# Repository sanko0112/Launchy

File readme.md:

### ESP32 ESP-NOW Based model rocket launch controller

## 🤌Features

- ESP-NOW Long range protocol
- Multi-layer safety: Key switch, iButton, push button
- OLED display for status feedback
- Built in battery charging circuit (TP4056)
- USB-C for programming/charging
- Internal 1S / External 2S battery selection for the e-match
- Continuity test (1S mode)
- Preheat mode(1S mode)
- Configurabe Countdown time, Ignition time
## 🔧Hardware

&nbsp;&nbsp;&nbsp;&nbsp;&nbsp;The system is based on a custom PCB designed in KiCad, built around the ESP32-C3-MINI-1 module. Both the transmitter and the igniter/receiver use the same board design, but are populated with different component sets depending on their role. The
hardware integrates Li-Ion charging (TP4056), a 3.3 V LDO regulator (AP2112K), a MOSFET-driven relay interface, iButton authentication, and status LEDs. USB-C is provided for charging and programming, while screw terminals allow safe connection of the igniter circuit.

&nbsp;&nbsp;&nbsp;&nbsp;&nbsp;Complete manufacturing files are available as a ZIP inside the GERBER folder as well as the BoM. Symbol and footprint libraries are uploaded so the project should be fully editable in KiCad now.

## 💻Firmware
### Transmitter.ino
- Handles the remote unit (user interface + iButton authentication).
- Implements menus for:
    - Battery type selection
    - Continuity check
    - Countdown time
    - Preheat start time
    - Preheat duration
    - Ignition delta
- Uses ESP-NOW to send launch and continuity test commands
- Provides OLED display feedback via LaunchDisplayLibrary
- Requires valid iButton for arming and launch
### Receiver.ino
- Handles the receiver unit (relay + buzzer)
- Waits for commands over ESP-NOW
- Performs continuity test by measuring V<sub>drop<sub>
- Executes countdown, preheat, and ignition relay control
- Includes buzzer startup sounds and launch feedback
### LaunchDisplayLibrary
- Custom display driver using U8g2 for SH1106 OLED.
- Provides functions for:
    - Splash/welcome screen
    - Authentication animations
    - Armed state screen (with T-, P_s, P_d, I_d values)
    - Countdown + preheat visual feedback
    - Ignition screen
    - Menus for parameter selection
### GetMacAddress.ino
- Utility to print the ESP32’s MAC address (used for setting ESP-NOW peers).
### ReadFob.ino
- Utility to read and print iButton IDs (used to whitelist authorized keys).
### Dependencies
#### [Arduino Core for ESP32](https://github.com/espressif/arduino-esp32)
### Libraries:
- esp_now.h (built-in)
- WiFi.h (built-in)
- esp_wifi.h (for long-range protocol mode)
- OneWire (for iButton reader)
- U8g2lib (for OLED display)
## 🚀 Setup & Upload
1. Clone repo and open in Arduino IDE.
2. Select ESP32 Dev Module (or your ESP32 board).
3. Upload separately:
    - Transmitter.ino → Remote unit
    - 2.Receiver.ino → Receiver unit
4. Use GetMacAddress.ino on each ESP32 to note their MAC addresses.
    - Update broadcastAddress[] in transmitter/receiver code accordingly.
5. Use Read_fob.ino to read your iButton ID.
    - Replace in allowedID[] array in the transmitter code.
## 📺 Display demo

## 🔒 Safety

- Relay will not activate without valid iButton authentication.
- Launch packets use a session_id to prevent accidental re-triggering.
- Continuity test ensures igniter is properly connected before launch, if fails the system enters failsafe, requires full restart
## ✏️Schematic

## 📷Images

### Transmitter

### Igniter

### Accessories

## 🎥Demo

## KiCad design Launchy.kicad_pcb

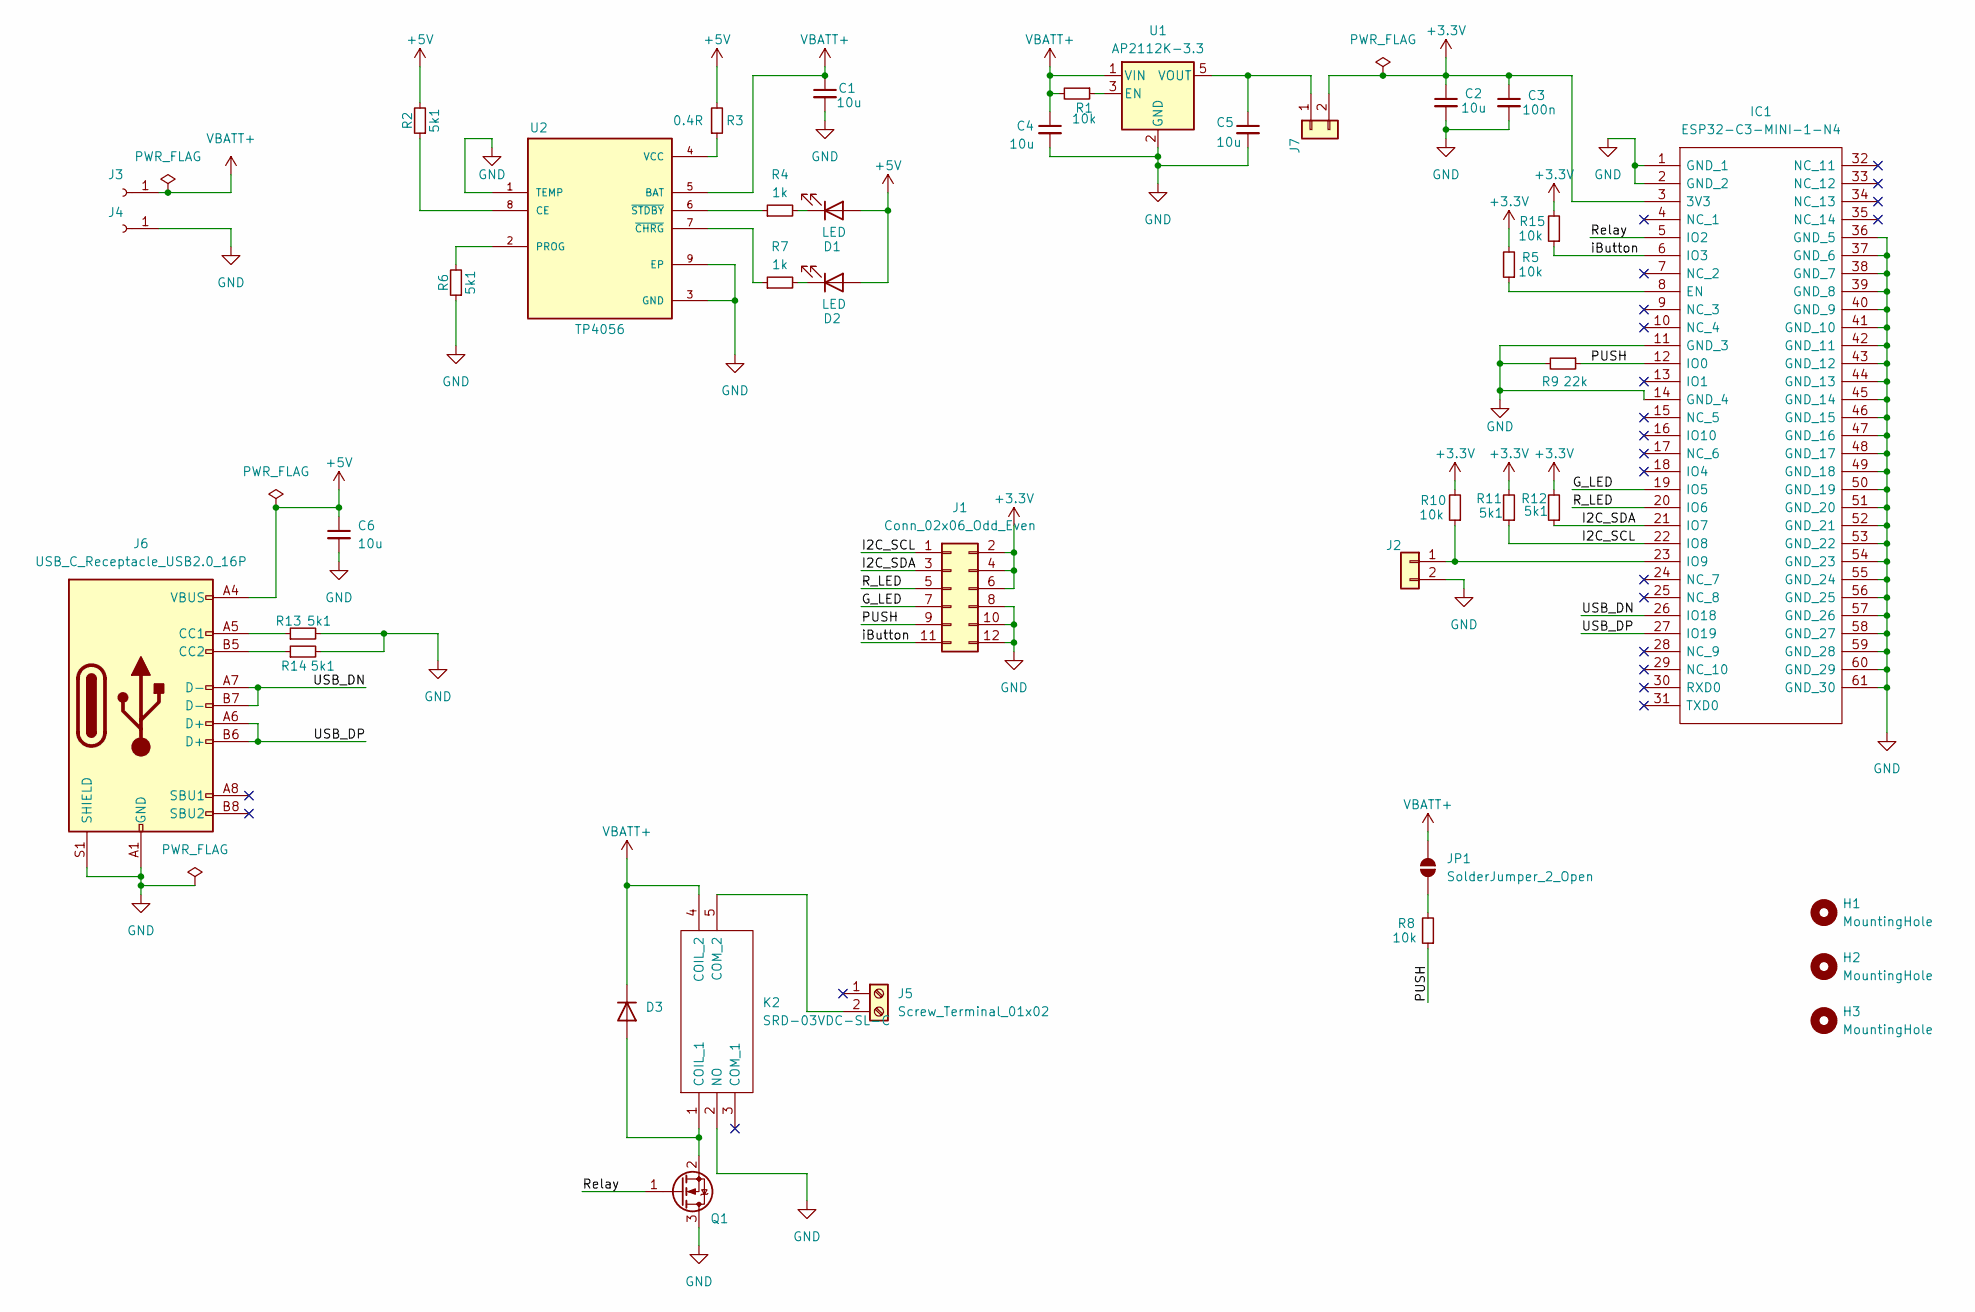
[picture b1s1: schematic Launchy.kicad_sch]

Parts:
C1, C2, C4, C5, C6: 10u; C_1206_3216Metric_Pad1.33x1.80mm_HandSolder
C3: 100n; C_1206_3216Metric_Pad1.33x1.80mm_HandSolder
D1, D2: LED; LED_1206_3216Metric_Pad1.42x1.75mm_HandSolder
D3: D_DO-201AD_P15.24mm_Horizontal
H1, H2, H3: MountingHole; MountingHole_3.2mm_M3
IC1: ESP32-C3-MINI-1-N4; ESP32C3MINI1N4; Manufacturer_Part_Number ESP32-C3-MINI-1-N4; Mouser Part Number 356-ESP32-C3-MINI1N4
J1: Conn_02x06_Odd_Even; PinHeader_2x06_P2.54mm_Vertical
J2, J7: Conn_01x02; PinHeader_1x02_P2.54mm_Vertical
J3, J4: Conn_01x01_Socket; SolderWirePad_1x01_SMD_4x4mm
J5: Screw_Terminal_01x02; TerminalBlock_MaiXu_MX126-5.0-02P_1x02_P5.00mm
J6: USB_C_Receptacle_USB2.0_16P; USB_C_Receptacle_GCT_USB4105-xx-A_16P_TopMnt_Horizontal
JP1: SolderJumper_2_Open; SolderJumper-2_P1.3mm_Open_TrianglePad1.0x1.5mm
K2: SRD-03VDC-SL-C; SRD03VDCSLC; Manufacturer_Part_Number SRD-03VDC-SL-C
Q1: IRLML0030; SOT-23
R1, R5, R8, R10, R15: 10k; C_1206_3216Metric_Pad1.33x1.80mm_HandSolder
R2, R6, R11, R12, R13, R14: 5k1; C_1206_3216Metric_Pad1.33x1.80mm_HandSolder
R3: 0.4R; C_1206_3216Metric_Pad1.33x1.80mm_HandSolder
R4, R7: 1k; C_1206_3216Metric_Pad1.33x1.80mm_HandSolder
R9: 22k; C_1206_3216Metric_Pad1.33x1.80mm_HandSolder
U1: AP2112K-3.3; SOT-23-5
U2: TP4056; SOP127P600X175-9N

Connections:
+3.3V: C2.1, C3.1, IC1.3 (3V3), J1.2, J1.4, J1.6, J7.2, R5.2, R10.2, R11.2, R12.2, R15.2
+5V: C6.1, D1.2 (A), D2.2 (A), J6.A4 (VBUS), J6.A9 (VBUS), J6.B4 (VBUS), J6.B9 (VBUS), R2.2, R3.2
/G_LED: IC1.19 (IO5), J1.7
/I2C_SCL: IC1.22 (IO8), J1.1, R11.1
/I2C_SDA: IC1.21 (IO7), J1.3, R12.1
/PUSH: IC1.12 (IO0), J1.9, R8.1, R9.1
/R_LED: IC1.20 (IO6), J1.5
/Relay: IC1.5 (IO2), Q1.1 (G)
/USB_DN: IC1.26 (IO18), J6.A7 (D-), J6.B7 (D-)
/USB_DP: IC1.27 (IO19), J6.A6 (D+), J6.B6 (D+)
/iButton: IC1.6 (IO3), J1.11, R15.1
GND: C1.2, C2.2, C3.2, C4.2, C5.2, C6.2, IC1.1 (GND_1), IC1.2 (GND_2), IC1.11 (GND_3), IC1.14 (GND_4), IC1.36 (GND_5), IC1.37 (GND_6), IC1.38 (GND_7), IC1.39 (GND_8), IC1.40 (GND_9), IC1.41 (GND_10), IC1.42 (GND_11), IC1.43 (GND_12), IC1.44 (GND_13), IC1.45 (GND_14), IC1.46 (GND_15), IC1.47 (GND_16), IC1.48 (GND_17), IC1.49 (GND_18), IC1.50 (GND_19), IC1.51 (GND_20), IC1.52 (GND_21), IC1.53 (GND_22), IC1.54 (GND_23), IC1.55 (GND_24), IC1.56 (GND_25), IC1.57 (GND_26), IC1.58 (GND_27), IC1.59 (GND_28), IC1.60 (GND_29), IC1.61 (GND_30), J1.8, J1.10, J1.12, J2.2, J4.1, J6.A1 (GND), J6.A12 (GND), J6.B1 (GND), J6.B12 (GND), J6.S1 (SHIELD), K2.2 (NO), Q1.3 (D), R6.1, R9.2, R13.2, R14.2, U1.2 (GND), U2.1 (TEMP), U2.3 (GND), U2.9 (EP); also elsewhere on the board
unnamed: D1.1 (K), R4.2
unnamed: D2.1 (K), R7.2
unnamed: D3.2 (A), K2.1 (COIL_1), Q1.2 (S)
unnamed: IC1.8 (EN), R5.1
unnamed 16: IC1.23 (IO9), J2.1, R10.1; also elsewhere on the board
unnamed: J5.2, K2.5 (COM_2)
unnamed: J6.A5 (CC1), R13.1
unnamed: J6.B5 (CC2), R14.1
unnamed: C5.1, J7.1, U1.5 (VOUT)
unnamed: JP1.2 (B), R8.2
unnamed: R1.1, U1.3 (EN)
unnamed: R2.1, U2.8 (CE)
unnamed: R6.2, U2.2 (PROG)
unnamed: R3.1, U2.4 (VCC)
unnamed: R7.1, U2.7 (~CHRG)
unnamed: R4.1, U2.6 (~STDBY)
VBATT+: C1.1, C4.1, D3.1 (K), J3.1, JP1.1 (A), K2.4 (COIL_2), R1.2, U1.1 (VIN), U2.5 (BAT); also elsewhere on the board

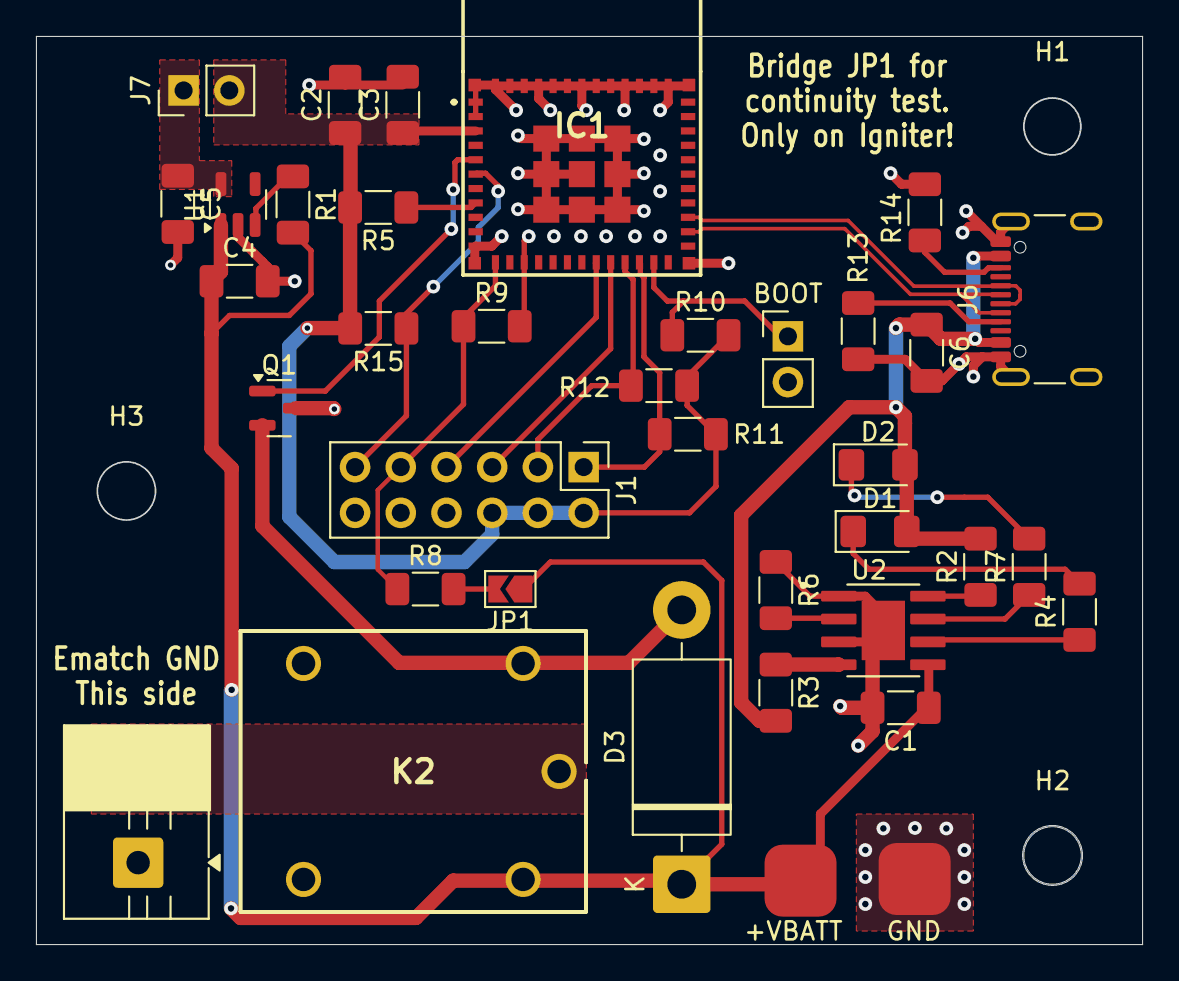
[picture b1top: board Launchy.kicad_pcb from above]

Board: 2 copper layers, 61.5 x 50.5 mm, 40 parts (0 on the bottom side), 29 nets.

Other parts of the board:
+VBATT: Conn_01x01_Socket; SolderWirePad_1x01_SMD_4x4mm
BOOT: Conn_01x02; PinHeader_1x02_P2.54mm_Vertical
GND: Conn_01x01_Socket; SolderWirePad_1x01_SMD_4x4mm

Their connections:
GND: BOOT.2, GND.1; also elsewhere on the board
unnamed 16: BOOT.1; also elsewhere on the board
VBATT+: +VBATT.1; also elsewhere on the board

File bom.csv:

Designator,Footprint,Quantity,Value,LCSC Part #
"C1, C2, C4, C5, C6",1206,5,10u,
C3,1206,1,100n,
"D1, D2",1206,2,LED,
D3,D_DO-201AD_P15.24mm_Horizontal,1,~,
IC1,ESP32C3MINI1N4,1,ESP32-C3-MINI-1-N4,
IC2,SOT65P210X110-6N,1,SBC846BPDW1T3G,
J1,PinHeader_2x06_P2.00mm_Vertical,1,Conn_02x06_Odd_Even,
J2,PinHeader_1x02_P2.54mm_Vertical,1,Conn_01x02,
"J3, J4",SolderWirePad_1x01_SMD_4x4mm,2,Conn_01x01_Socket,
J5,PinSocket_1x03_P2.54mm_Vertical,1,Screw_Terminal_01x03,
J6,USB_C_Receptacle_GCT_USB4105-xx-A_16P_TopMnt_Horizontal,1,USB_C_Receptacle_USB2.0_16P,
K1,SRD03VDCSLC,1,SRD-03VDC-SL-C,
Q1,SOT-23,1,IRLML0030,
"R1, R10, R5, R9",1206,4,10k,
"R11, R12, R13, R14, R2, R6",1206,6,5k1,
R3,1206,1,0.4R,
"R4, R7",1206,2,1k,
SW1,PinHeader_1x03_P2.00mm_Vertical,1,SW_SPDT,
U1,SOT-23-5,1,AP2112K-3.3,
U2,SOP127P600X175-9N,1,TP4056,

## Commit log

2025-09-19 updated logo color for visibility, fix for images not appearing
2025-09-19 Fixed picture naming
2025-09-19 Filename fix
2025-09-19 Create LICENSE
2025-09-20 Quality of life changes in Code Symbol and footprint libraries include Schematic and pcb updates, unnecessary dual bjt remove, replacing 2.00mm headers with more common 2.54mm ones Copper Pour tweaks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
2025-09-20 updated Schematic in README
2025-09-23 updated graphics
2025-09-24 added board 3d model
2025-09-24 deleted unnecesary 3D models
2025-09-24 swapped stl models to stp for extra texture
